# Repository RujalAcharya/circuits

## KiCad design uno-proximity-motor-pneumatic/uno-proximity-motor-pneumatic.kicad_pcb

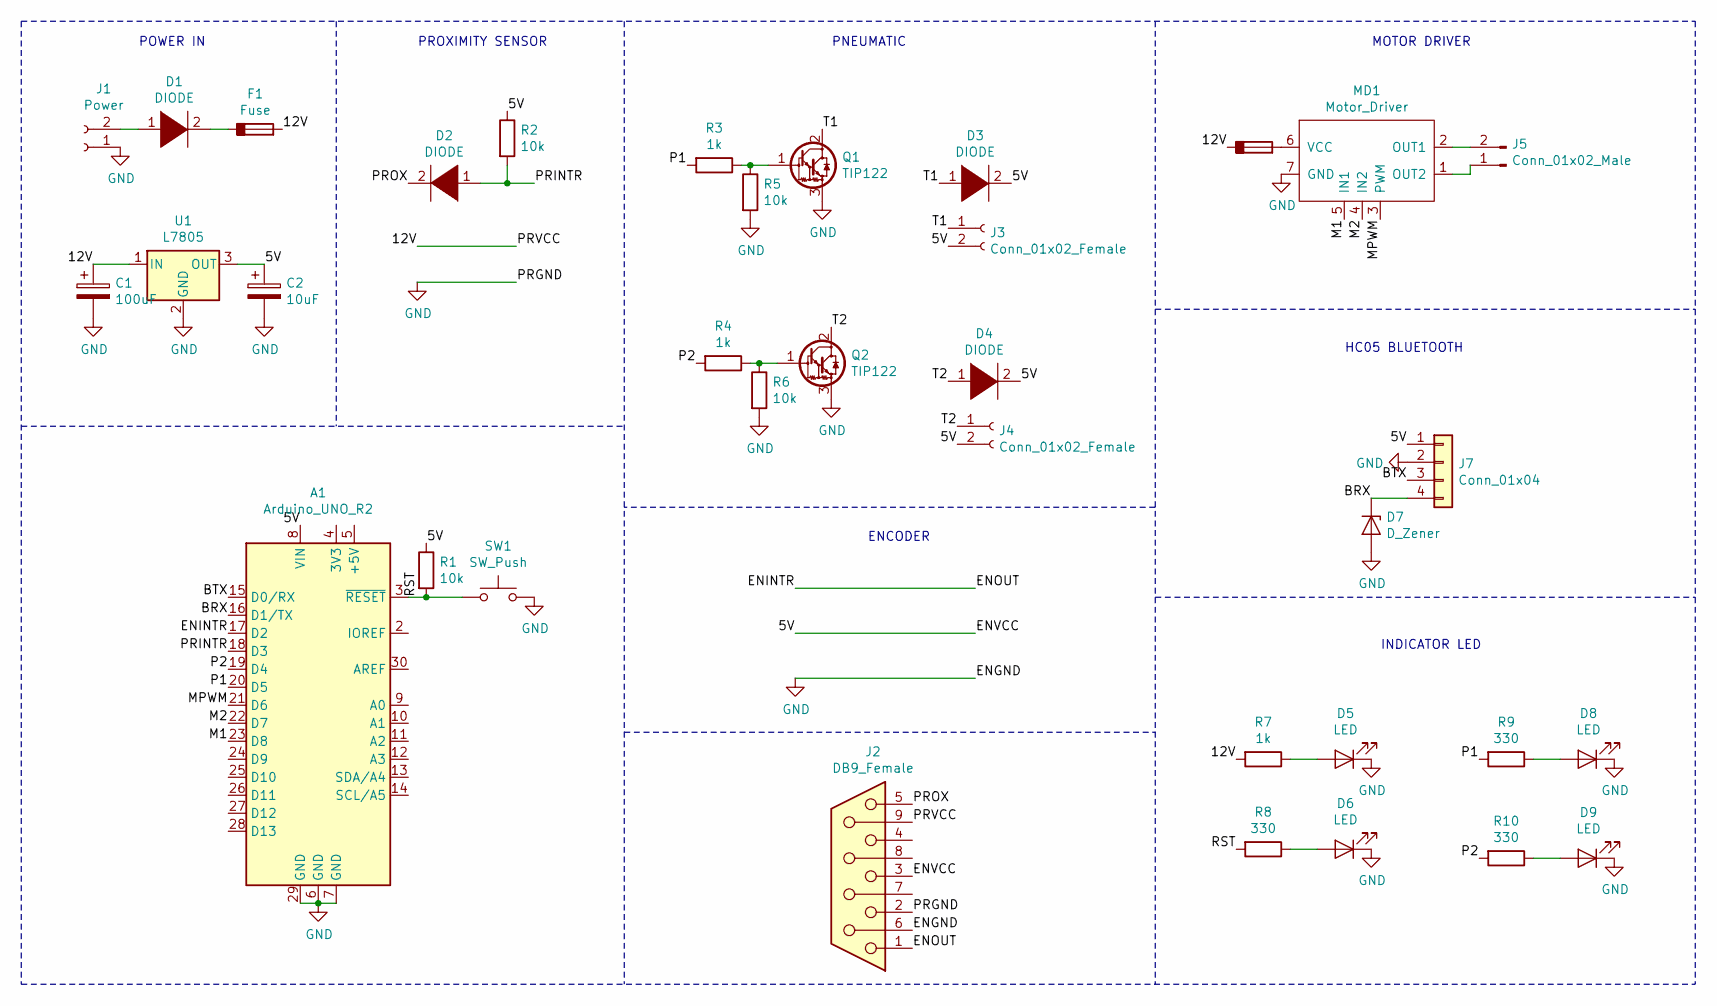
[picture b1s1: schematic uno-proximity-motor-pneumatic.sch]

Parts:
A1: Arduino_UNO_R2
C1: 100uF; Capacitor_100uF
C2: 10uF; Capacitor_10uF
D1: DIODE; Diode_Medium
D2, D3, D4: DIODE; Diode_Small
D5: LED; LED_D5.0mm
D6, D8, D9: LED; LED_D3.0mm
D7: D_Zener; Diode_Small
F1, F2: Fuse; Fuse_Holder
J1: Power; Solar_Connector
J2: DB9_Female; Connector_DB_9
J3, J4: Conn_01x02_Female; Connector_Bornier_2
J5: Conn_01x02_Male; Solar_Connector
J7: Conn_01x04; bluetooth
MD1: Motor_Driver; H_Bridge
Q1, Q2: TIP122; TO-220-3_Vertical
R1, R2, R5, R6: 10k; Resistor_small
R3, R4, R7: 1k; Resistor_small
R8, R9, R10: 330; Resistor_small
SW1: SW_Push; Push_Button
U1: L7805; Voltage_Regulators

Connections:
/5V: A1.8 (VIN), C2.1, D3.2 (A), D4.2 (A), J2.3, J3.2, J4.2, J7.1, R1.1, R2.1, U1.3 (OUT)
/12V: C1.1, F1.2, F2.1, J2.9, R7.2, U1.1 (IN)
/BRX: A1.16 (D1/TX), D7.1 (K), J7.4
/BTX: A1.15 (D0/RX), J7.3
/ENINTR: A1.17 (D2), J2.1
/M1: A1.23 (D8), MD1.5 (IN1)
/M2: A1.22 (D7), MD1.4 (IN2)
/MPWM: A1.21 (D6), MD1.3 (PWM)
/P1: A1.20 (D5), R3.2, R9.2
/P2: A1.19 (D4), R4.2, R10.2
/PRINTR: A1.18 (D3), D2.1 (K), R2.2
/PROX: D2.2 (A), J2.5
/RST: A1.3 (~RESET), R1.2, R8.2, SW1.1
/T1: D3.1 (K), J3.1, Q1.2 (C)
/T2: D4.1 (K), J4.1, Q2.2 (C)
GND: A1.6 (GND), A1.7 (GND), A1.29 (GND), C1.2, C2.2, D5.1 (K), D6.1 (K), D7.2 (A), D8.1 (K), D9.1 (K), J1.1, J2.2, J2.6, J7.2, MD1.7 (GND), Q1.3 (E), Q2.3 (E), R5.2, R6.2, SW1.2, U1.2 (GND)
unnamed: D1.1 (K), J1.2
unnamed: D1.2 (A), F1.1
unnamed: D5.2 (A), R7.1
unnamed: D6.2 (A), R8.1
unnamed: D8.2 (A), R9.1
unnamed: D9.2 (A), R10.1
unnamed: F2.2, MD1.6 (VCC)
unnamed: J5.1, MD1.1 (OUT2)
unnamed: J5.2, MD1.2 (OUT1)
unnamed: Q1.1 (B), R3.1, R5.1
unnamed: Q2.1 (B), R4.1, R6.1

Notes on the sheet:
POWER IN
PROXIMITY SENSOR
PNEUMATIC
ENCODER
MOTOR DRIVER
INDICATOR LED
HC05 BLUETOOTH

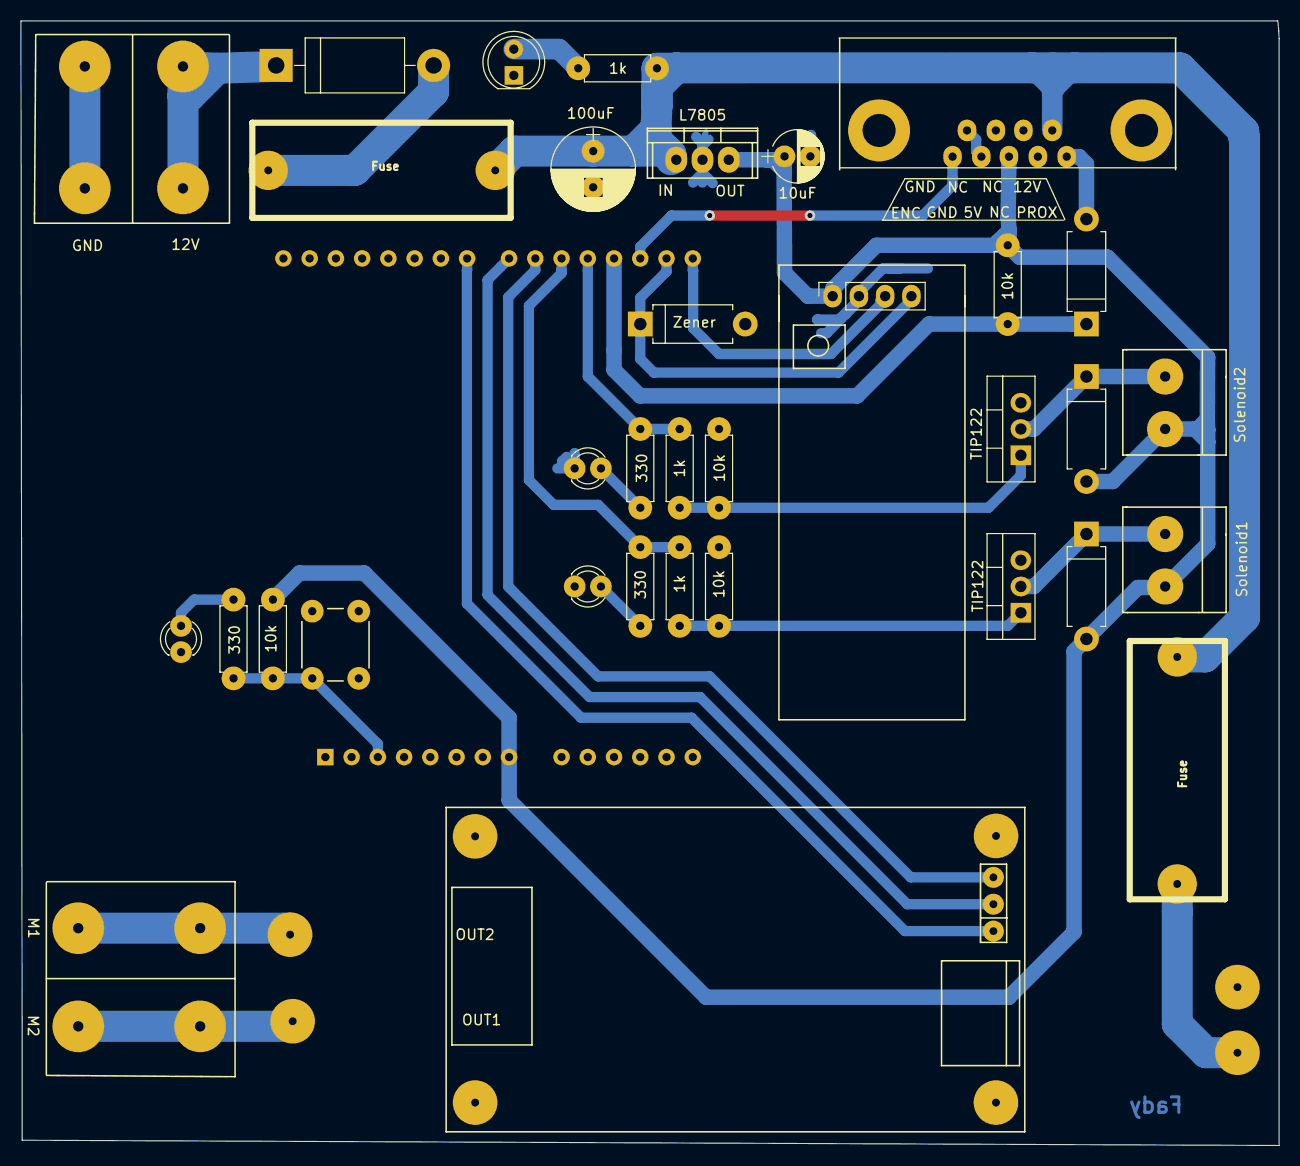
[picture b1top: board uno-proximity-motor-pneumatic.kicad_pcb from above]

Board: 2 copper layers, 121.8 x 108.8 mm, 35 parts (1 on the bottom side), 27 nets.

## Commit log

2021-08-07 Added 1st circuit
